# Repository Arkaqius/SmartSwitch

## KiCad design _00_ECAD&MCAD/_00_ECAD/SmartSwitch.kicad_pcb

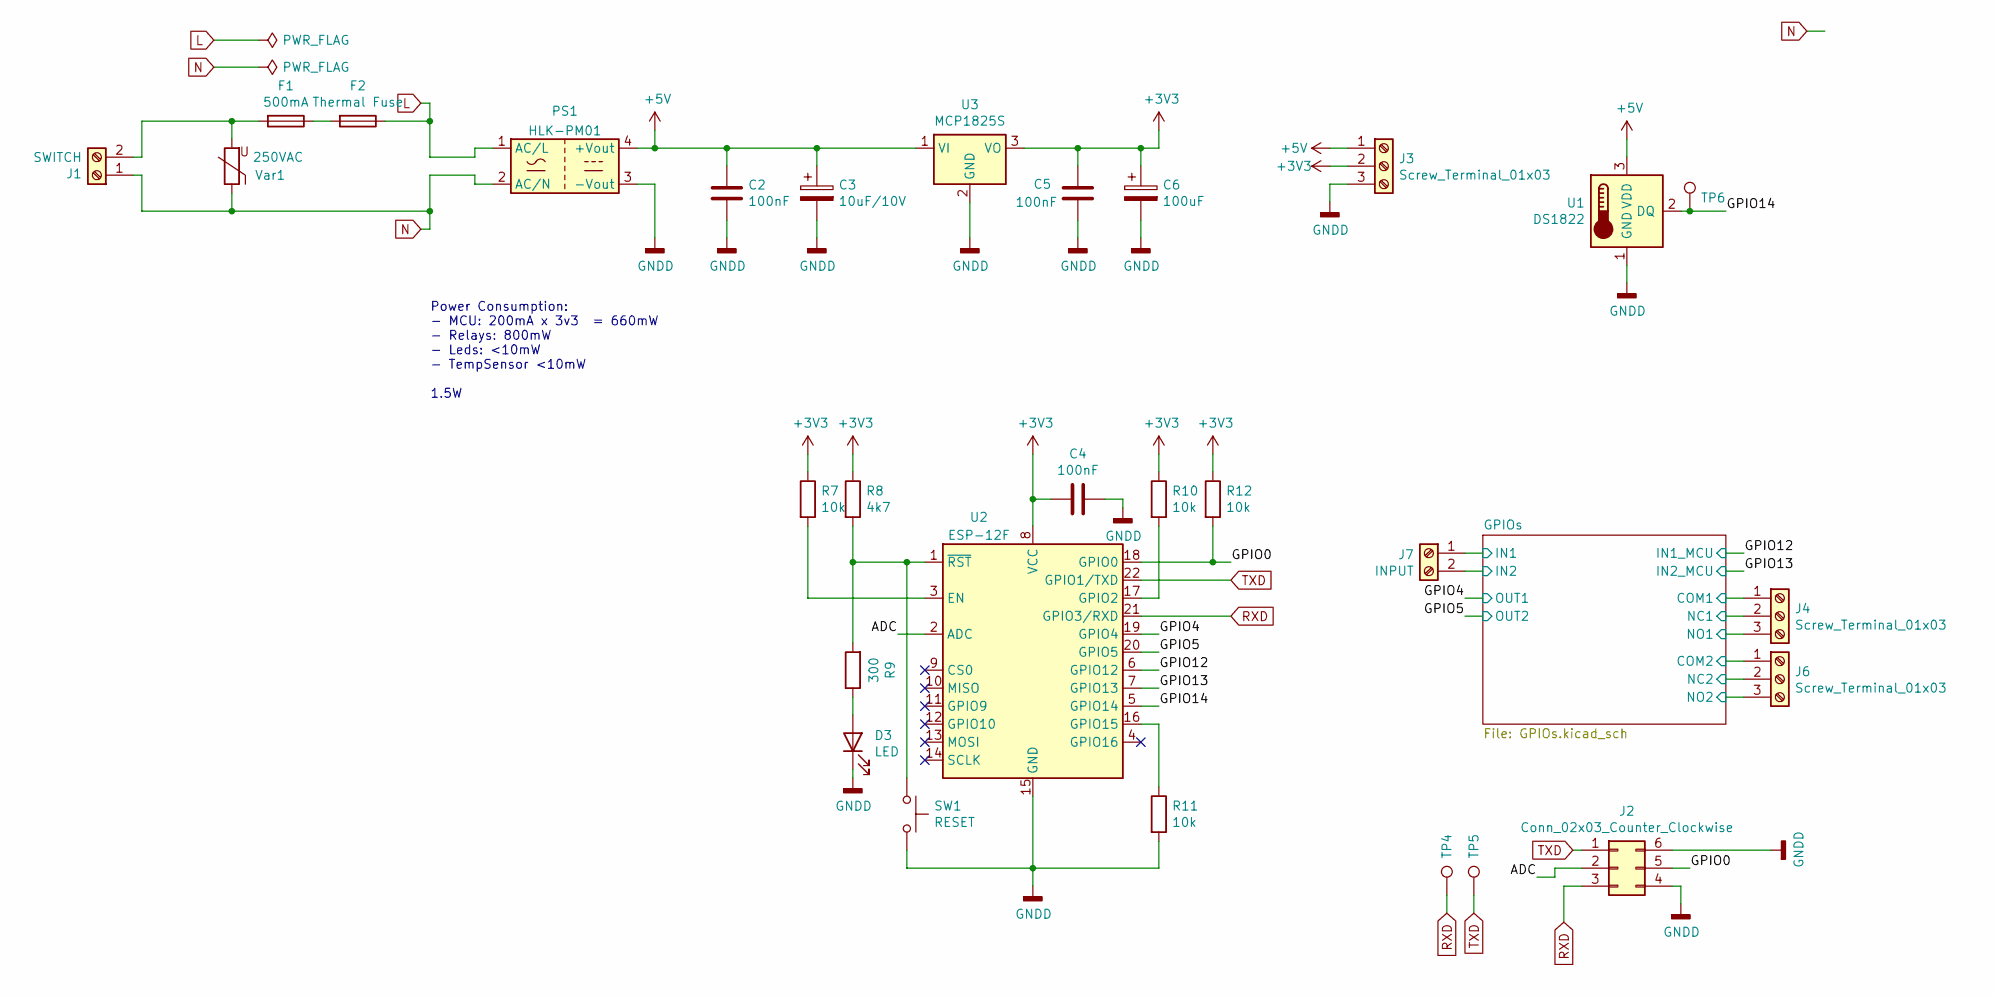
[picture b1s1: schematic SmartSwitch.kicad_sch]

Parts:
C2, C5: 100nF; C_Disc_D5.0mm_W2.5mm_P5.00mm
C3: 10uF/10V; CP_Radial_D5.0mm_P2.50mm
C4: 100nF; C_1206_3216Metric_Pad1.42x1.75mm_HandSolder
C6: 100uF; CP_Radial_D5.0mm_P2.50mm
D3: LED; LED_1206_3216Metric_Pad1.42x1.75mm_HandSolder
F1: 500mA; Fuseholder_Cylinder-5x20mm_Schurter_0031_8201_Horizontal_Op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
F2: Thermal Fuse; R_Axial_DIN0204_L3.6mm_D1.6mm_P5.08mm_Vertical
J1: SWITCH; TerminalBlock_Phoenix_MKDS-1,5-2_1x02_P5.00mm_Horizontal
J2: Conn_02x03_Counter_Clockwise; PinHeader_2x03_P2.54mm_Vertical_SMD
J3, J4, J6: Screw_Terminal_01x03; TerminalBlock_Phoenix_MKDS-1,5-3_1x03_P5.00mm_Horizontal
J7: INPUT; TerminalBlock_Phoenix_MKDS-1,5-2_1x02_P5.00mm_Horizontal
PS1: HLK-PM01; Converter_ACDC_HiLink_HLK-PMxx
R7, R10, R11, R12: 10k; R_1206_3216Metric_Pad1.42x1.75mm_HandSolder
R8: 4k7; R_1206_3216Metric_Pad1.42x1.75mm_HandSolder
R9: 300; R_1206_3216Metric_Pad1.42x1.75mm_HandSolder
SW1: RESET; SW_SPST_B3SL-1022P
TP4, TP5, TP6: TestPoint; TestPoint_Pad_D1.0mm
U1: DS1822; TO-92_Inline
U2: ESP-12F; ESP-12E
U3: MCP1825S; SOT-223
Var1: 250VAC; RV_Disc_D7mm_W3.4mm_P5mm

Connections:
+3V3: C4.2, C5.1, C6.1, J3.2, R7.1, R8.1, R10.1, R12.1, U2.8 (VCC), U3.3 (VO); also elsewhere on the board
+5V: C2.1, C3.1, J3.1, PS1.4 (+Vout), U1.3 (VDD), U3.1 (VI); also elsewhere on the board
/ADC: J2.2, U2.2 (ADC)
/GPIO0: J2.5, R12.2, U2.18 (GPIO0)
/GPIO4: U2.19 (GPIO4); also elsewhere on the board
/GPIO5: U2.20 (GPIO5); also elsewhere on the board
/GPIO12: U2.6 (GPIO12); also elsewhere on the board
/GPIO13: U2.7 (GPIO13); also elsewhere on the board
/GPIO14: TP6.1, U1.2 (DQ), U2.5 (GPIO14)
/GPIOs/COM1: J4.1; also elsewhere on the board
/GPIOs/COM2: J6.1; also elsewhere on the board
/GPIOs/IN1: J7.1; also elsewhere on the board
/GPIOs/IN2: J7.2; also elsewhere on the board
/GPIOs/NC1: J4.2; also elsewhere on the board
/GPIOs/NC2: J6.2; also elsewhere on the board
/GPIOs/NO1: J4.3; also elsewhere on the board
/GPIOs/NO2: J6.3; also elsewhere on the board
GNDD: C2.2, C3.2, C4.1, C5.2, C6.2, D3.1 (K), J2.4, J2.6, J3.3, PS1.3 (-Vout), R11.2, SW1.2, U1.1 (GND), U2.15 (GND), U3.2 (GND); also elsewhere on the board
L: F2.1, PS1.1 (AC/L)
N: J1.1, PS1.2 (AC/N), Var1.1
unnamed: D3.2 (A), R9.1
unnamed: F1.1, F2.2
unnamed: F1.2, J1.2, Var1.2
unnamed: R7.2, U2.3 (EN)
unnamed: R8.2, R9.2, SW1.1, U2.1 (~RST)
unnamed: R10.2, U2.17 (GPIO2)
unnamed: R11.1, U2.16 (GPIO15)
RXD: J2.3, TP4.1, U2.21 (GPIO3/RXD)
TXD: J2.1, TP5.1, U2.22 (GPIO1/TXD)

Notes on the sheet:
Power Consumption: - MCU: 200mA x 3v3 = 660mW - Relays: 800mW - Leds: <10mW - TempSensor <10mW ~{} 1.5W

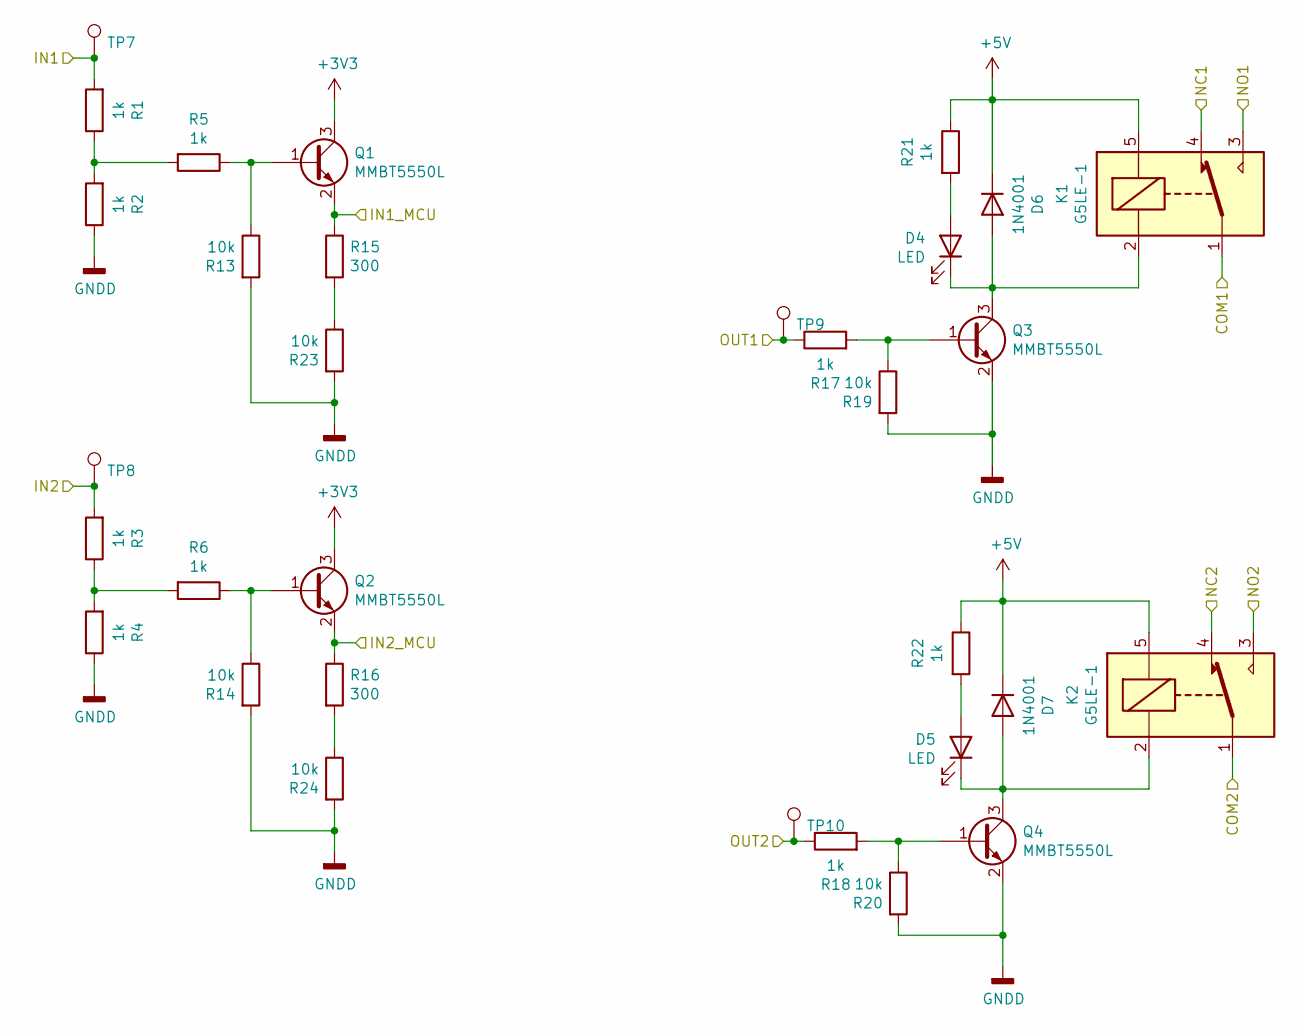
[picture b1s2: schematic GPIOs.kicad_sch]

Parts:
D4, D5: LED; LED_1206_3216Metric_Pad1.42x1.75mm_HandSolder
D6, D7: 1N4001; D_DO-41_SOD81_P10.16mm_Horizontal
K1, K2: G5LE-1; Relay_SPDT_Omron-G5LE-1
Q1, Q2, Q3, Q4: MMBT5550L; SOT-23
R1, R2, R3, R4, R5, R6, R17, R18, R21, R22: 1k; R_1206_3216Metric_Pad1.42x1.75mm_HandSolder
R13, R14, R19, R20: 10k; R_1206_3216Metric_Pad1.42x1.75mm_HandSolder
R15, R16: 300; R_1206_3216Metric_Pad1.42x1.75mm_HandSolder
R23, R24: 10k; R_1206_3216Metric_Pad1.30x1.75mm_HandSolder
TP7, TP8, TP9, TP10: TestPoint; TestPoint_Pad_D1.0mm

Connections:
+3V3: Q1.3 (C), Q2.3 (C); also elsewhere on the board
+5V: D6.1 (K), D7.1 (K), K1.5, K2.5, R21.1, R22.1; also elsewhere on the board
/GPIO4: R17.1, TP9.1; also elsewhere on the board
/GPIO5: R18.1, TP10.1; also elsewhere on the board
/GPIO12: Q1.2 (E), R15.1; also elsewhere on the board
/GPIO13: Q2.2 (E), R16.1; also elsewhere on the board
/GPIOs/COM1: K1.1; also elsewhere on the board
/GPIOs/COM2: K2.1; also elsewhere on the board
/GPIOs/IN1: R1.2, TP7.1; also elsewhere on the board
/GPIOs/IN2: R3.2, TP8.1; also elsewhere on the board
/GPIOs/NC1: K1.4; also elsewhere on the board
/GPIOs/NC2: K2.4; also elsewhere on the board
/GPIOs/NO1: K1.3; also elsewhere on the board
/GPIOs/NO2: K2.3; also elsewhere on the board
GNDD: Q3.2 (E), Q4.2 (E), R2.1, R4.1, R13.2, R14.2, R19.2, R20.2, R23.2, R24.2; also elsewhere on the board
unnamed: D4.1 (K), D6.2 (A), K1.2, Q3.3 (C)
unnamed: D4.2 (A), R21.2
unnamed: D5.1 (K), D7.2 (A), K2.2, Q4.3 (C)
unnamed: D5.2 (A), R22.2
unnamed: Q1.1 (B), R5.1, R13.1
unnamed: Q2.1 (B), R6.1, R14.1
unnamed: Q3.1 (B), R17.2, R19.1
unnamed: Q4.1 (B), R18.2, R20.1
unnamed: R1.1, R2.2, R5.2
unnamed: R3.1, R4.2, R6.2
unnamed: R15.2, R23.1
unnamed: R16.2, R24.1

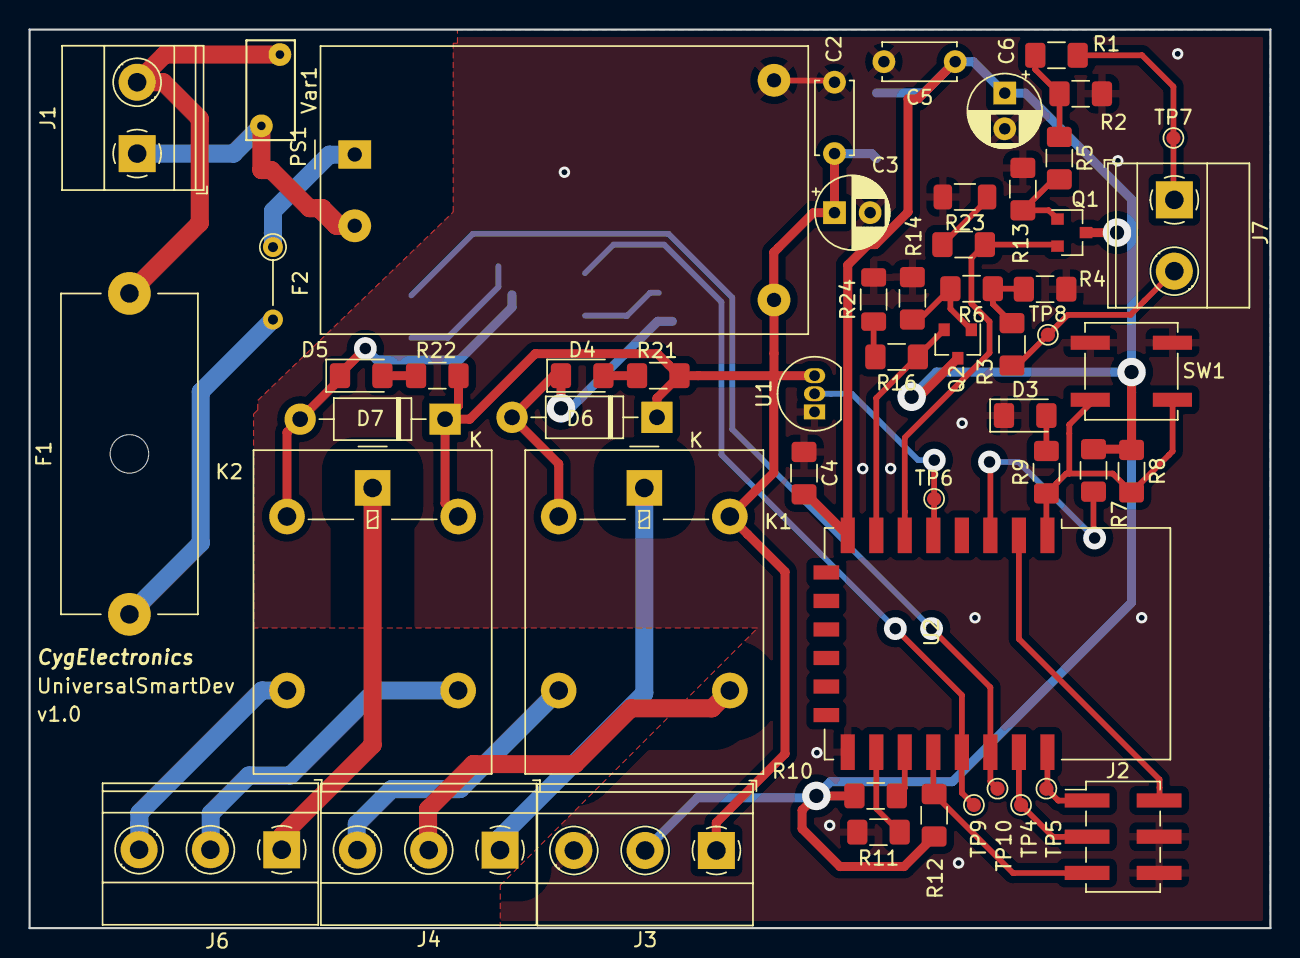
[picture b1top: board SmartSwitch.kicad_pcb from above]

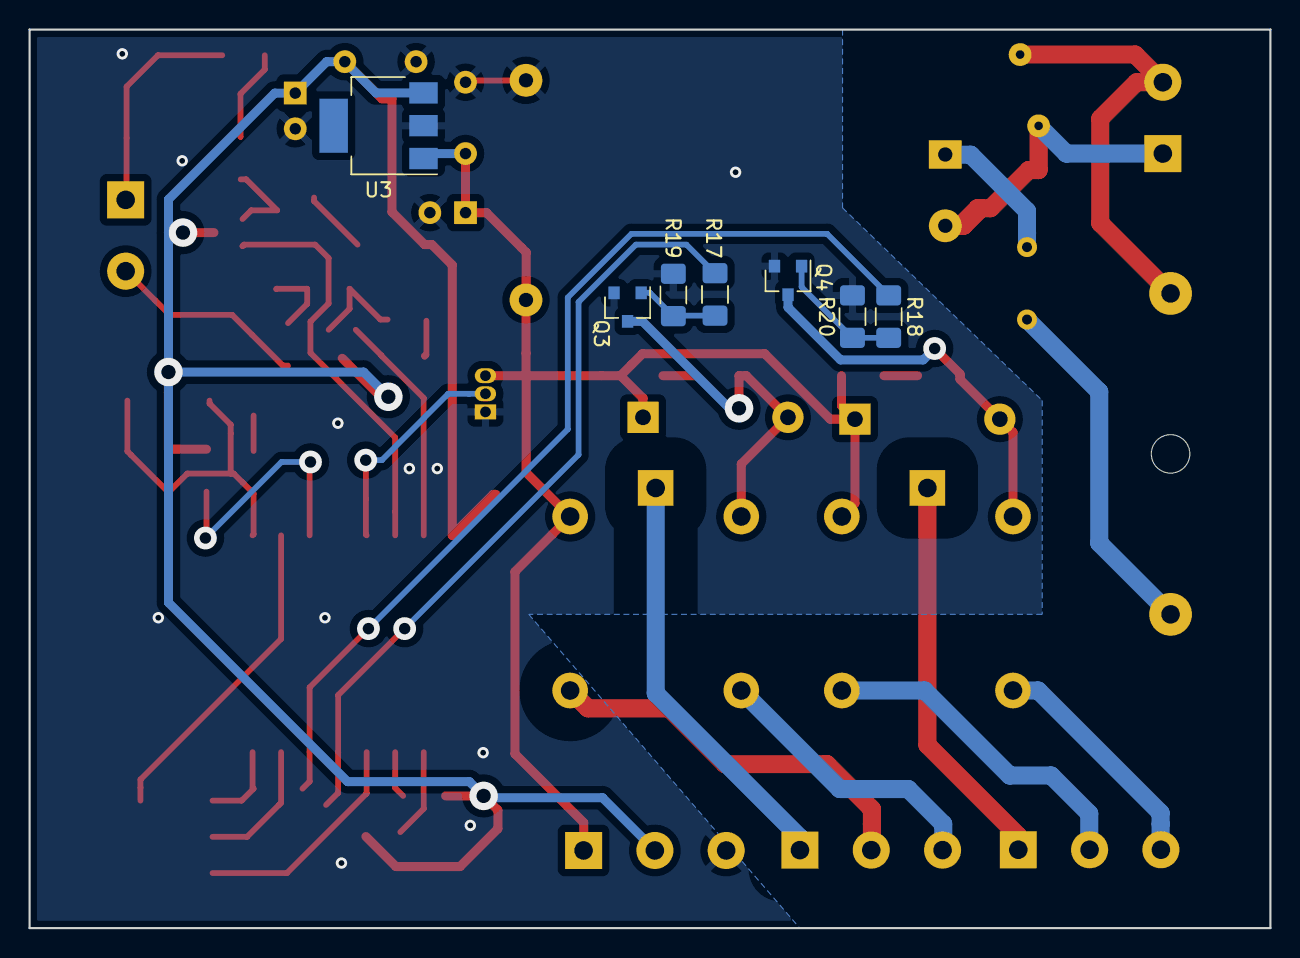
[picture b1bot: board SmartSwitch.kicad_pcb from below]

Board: 2 copper layers, 87.0 x 63.0 mm, 61 parts (7 on the bottom side), 41 nets.

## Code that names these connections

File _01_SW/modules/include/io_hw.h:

/*
 * io_hw.h
 *
 *  Created on: 20.02.2022
 *      Author: kulet
 */

#ifndef CORE_INCLUDE_IO_HW_H_
#define CORE_INCLUDE_IO_HW_H_

/*Inlcudes*/
#include "stdint.h"


/*Public defines*/
#define ADC_INPUT_PIN 2
/*Public enums*/



typedef enum INPUT_PINS {
	INPUT_1 = 12, /*GPIO12*/
	INPUT_2 = 13, /*GPIO13*/
}in_pin_t;

typedef enum OUTPUT_PINS {
	RELAY_1_OUT = 4 /*GPIO4*/,
	RELAY_2_OUT = 5 /*GPIO5*/,
}out_pin_t;

typedef enum PIN_STATE{
	CLEAR 	= 	0,
	SET		=	1
}pin_state_t;

/*Output interface */
void io_hw_init(void);

pin_state_t io_hw_get_pin(out_pin_t pin);

void io_hw_set_pin(out_pin_t pin,pin_state_t state);

#endif /* CORE_INCLUDE_IO_HW_H_ */

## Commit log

2022-10-03 First release
2022-10-04 Fix LED, common emitter issue, add adc feature
